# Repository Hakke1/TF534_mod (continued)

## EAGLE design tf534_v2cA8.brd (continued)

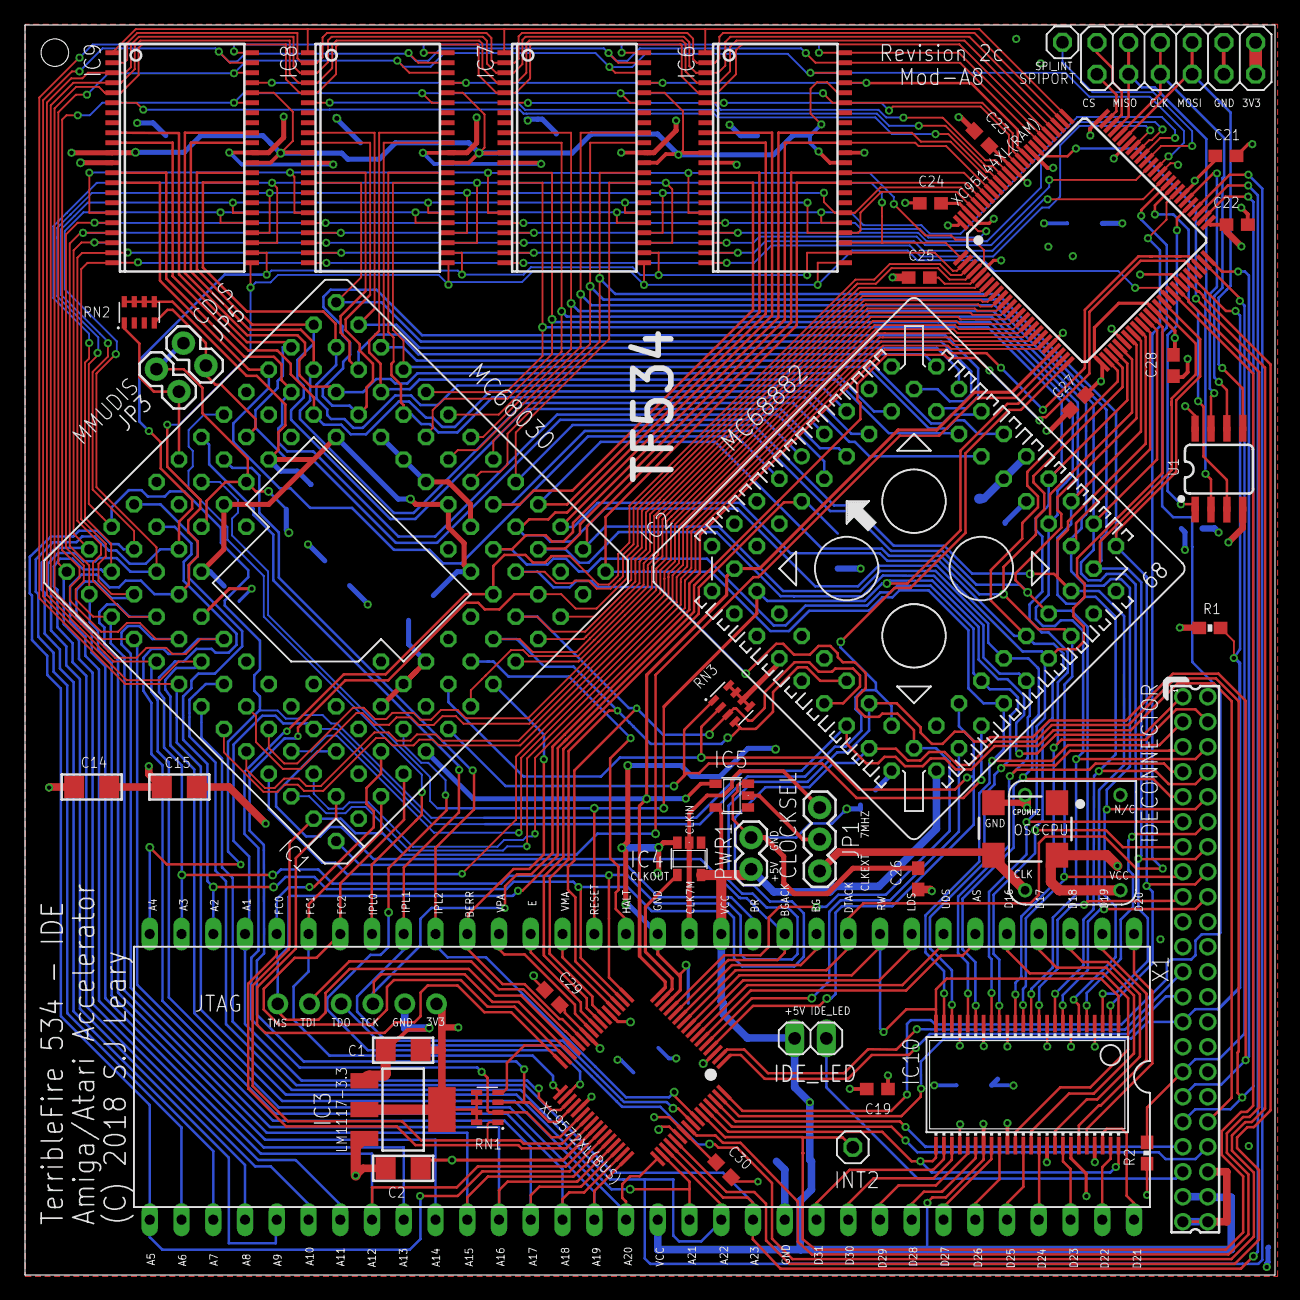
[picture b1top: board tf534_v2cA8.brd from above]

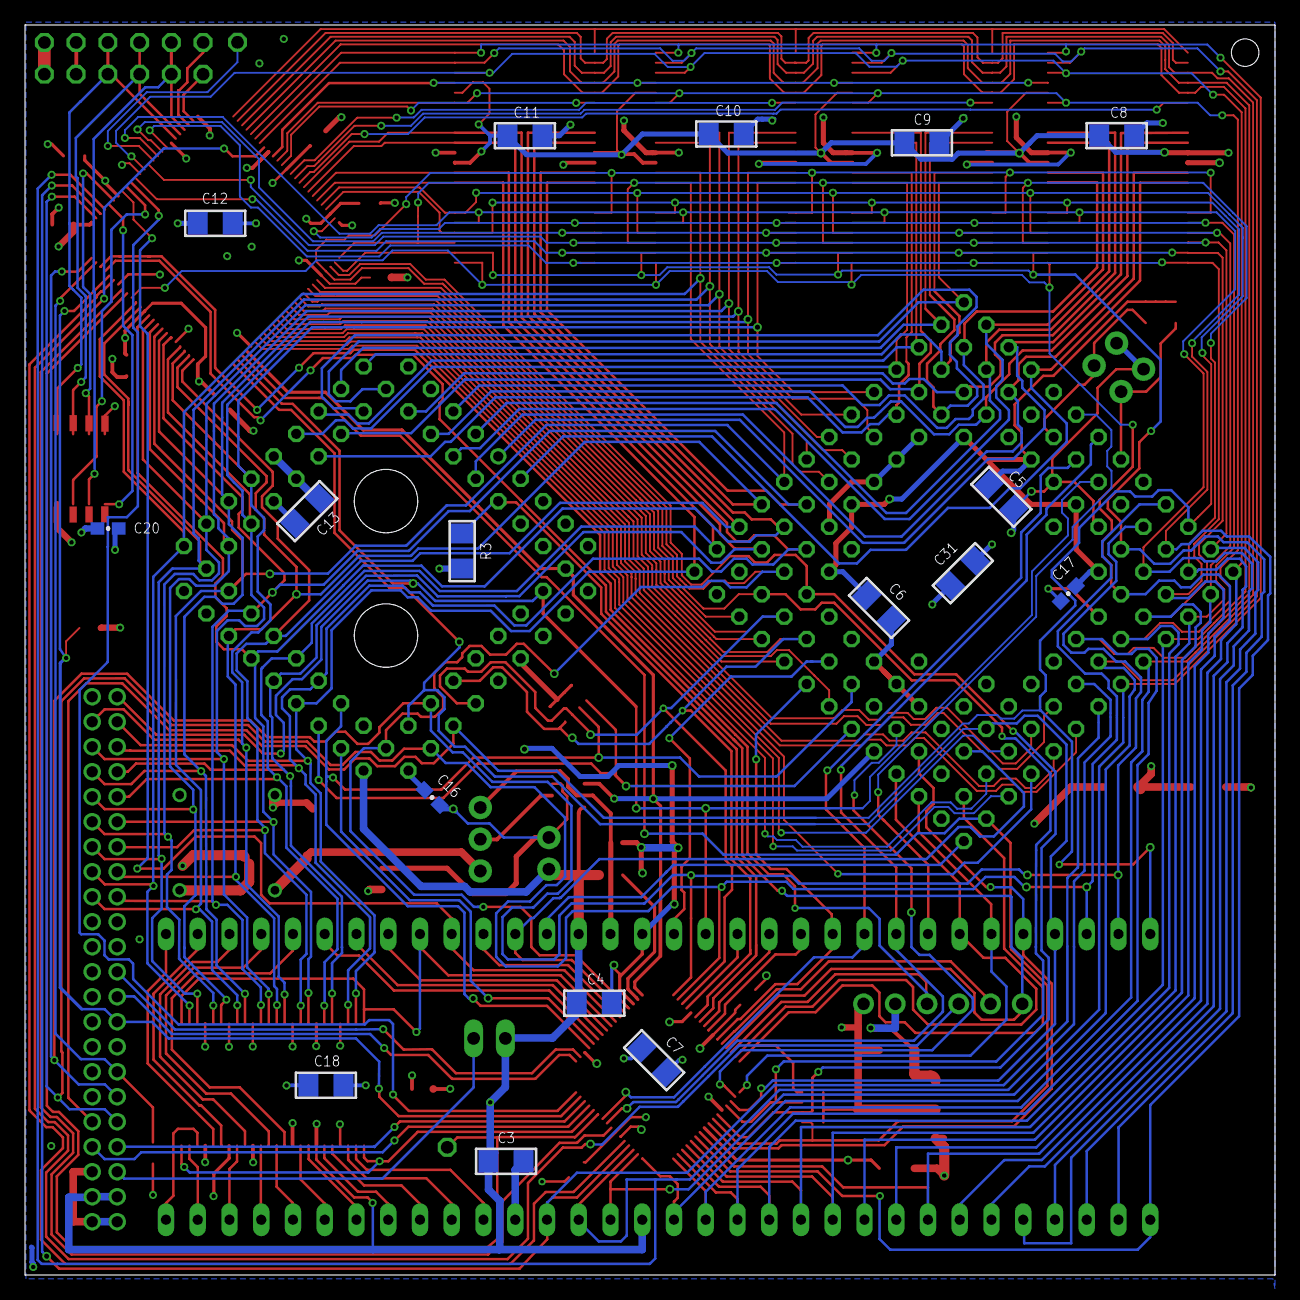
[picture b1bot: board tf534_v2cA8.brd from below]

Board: 4 copper layers, 100.0 x 100.0 mm, 62 parts (17 on the bottom side), 157 nets.
